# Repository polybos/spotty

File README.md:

# Spotty

Lounge- und andere Beleuchtung für das Netz39.
u.a. Treiber für 1A-LEDs 5V mit PWM (CAT4101).

http://www.netz39.de/wiki/projects:2016:spotty

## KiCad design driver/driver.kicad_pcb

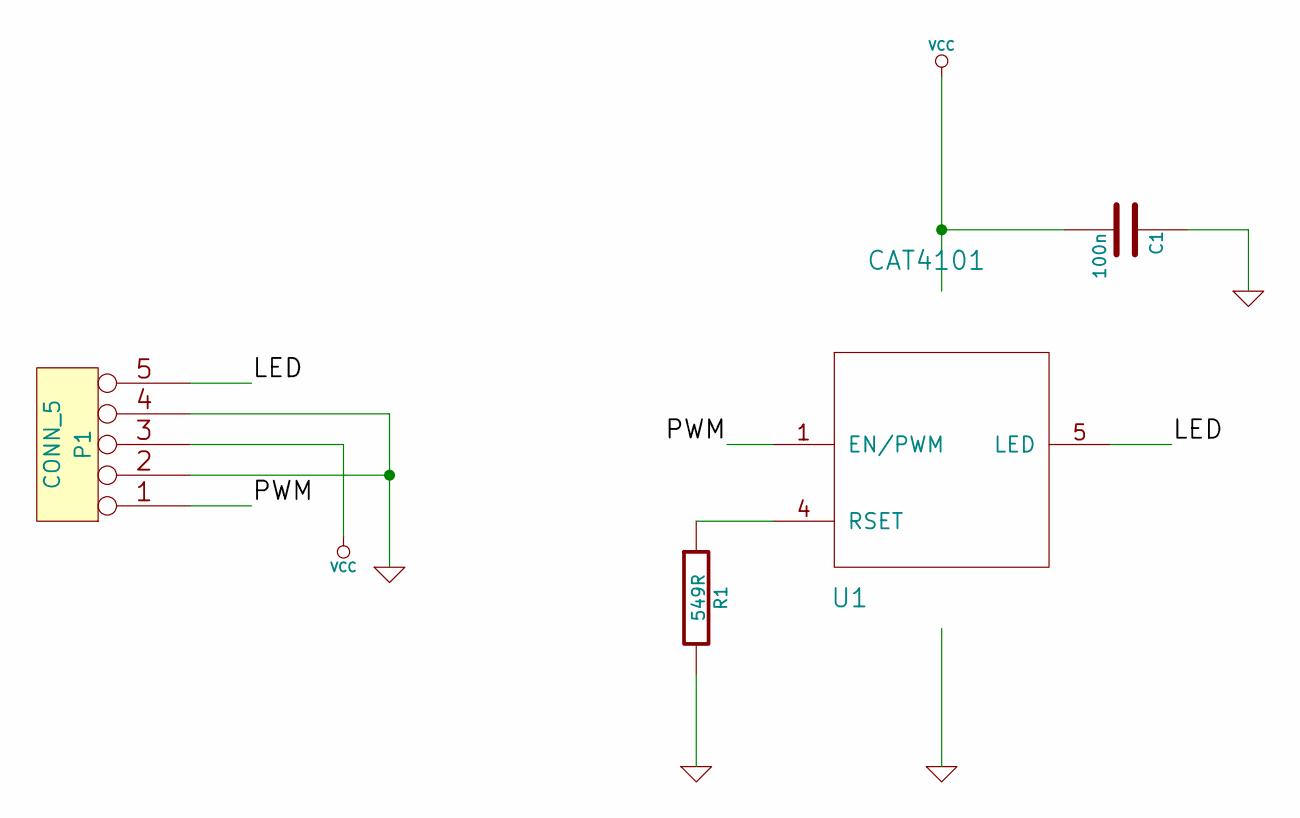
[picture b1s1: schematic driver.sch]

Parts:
C1: 100n
P1: CONN_5
R1: 549R
U1: CAT4101

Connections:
/LED: P1.5, U1.5 (LED)
/PWM: P1.1, U1.1 (EN/PWM)
GND: C1.1, P1.2, P1.4, R1.2, U1.3 (GND)
unnamed: R1.1, U1.4 (RSET)
VCC: C1.2, P1.3, U1.2 (VCC)

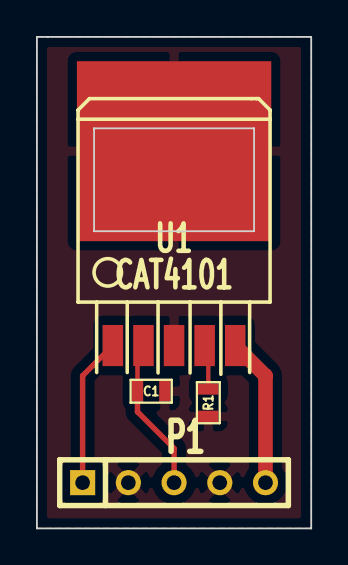
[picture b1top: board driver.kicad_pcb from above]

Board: 2 copper layers, 15.2 x 27.3 mm, 4 parts (0 on the bottom side), 5 nets.

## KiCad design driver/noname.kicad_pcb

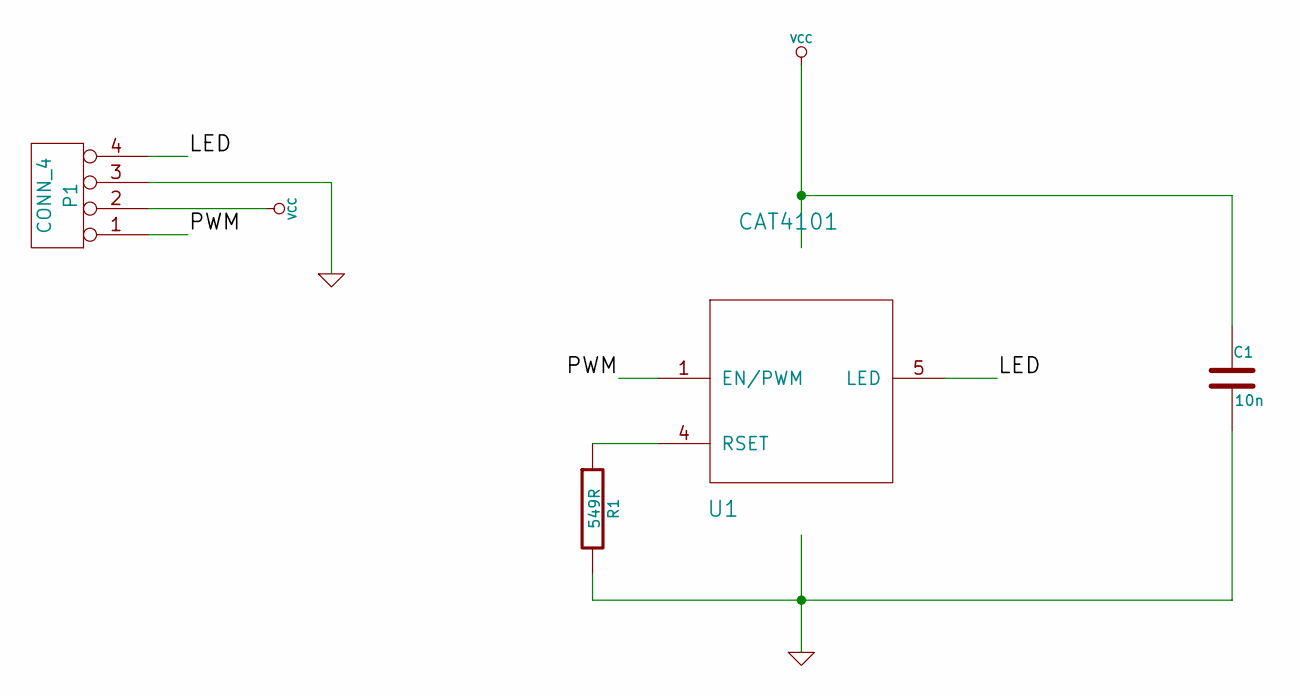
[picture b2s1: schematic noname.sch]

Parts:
C1: 10n
P1: CONN_4
R1: 549R
U1: CAT4101

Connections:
/LED: P1.4, U1.5 (LED)
/PWM: P1.1, U1.1 (EN/PWM)
GND: C1.2, P1.3, R1.2, U1.3 (GND)
unnamed: R1.1, U1.4 (RSET)
VCC: C1.1, P1.2, U1.2 (VCC)

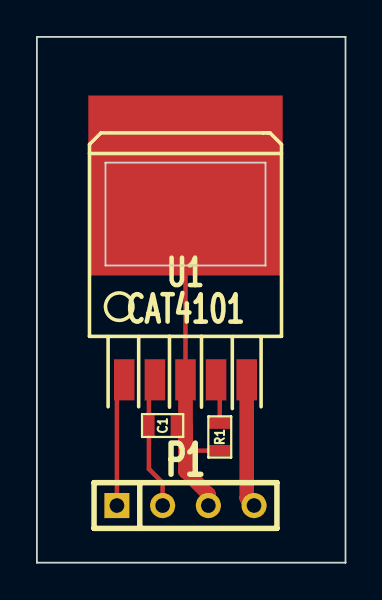
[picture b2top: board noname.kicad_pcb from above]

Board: 2 copper layers, 17.1 x 29.2 mm, 4 parts (0 on the bottom side), 5 nets.

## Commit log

2016-11-05 I2C parts library for KiCad
2016-11-05 N39 parts library for KiCad
2016-11-05 Update of CAT4101 in N39 lib
2016-11-06 LED driver
2016-11-06 LED driver projectified
2016-11-06 And now with files
2016-11-06 Insert ground plane
